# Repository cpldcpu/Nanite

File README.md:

Nanite 85 
======

The Nanite 85, a nano-sized ATtiny85 devboard with USB Bootloader - most likely the smallest one ever.

The repository holds the Eagle circuit, PCB design data and a software example to handle the soft reset-button.

See [Blog post](http://cpldcpu.wordpress.com/2014/04/25/the-nanite-85/) for more information.

New
===

I teamed up with [Watterott](http://www.watterott.com) on making the Nanite 85 available for everyone. You can get one [here](http://www.watterott.com/de/Wattuino-Nanite85). Note that changes had to be made for manufacturability.

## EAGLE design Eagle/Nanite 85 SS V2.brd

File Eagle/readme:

Version 2 of the Single Sided Layout

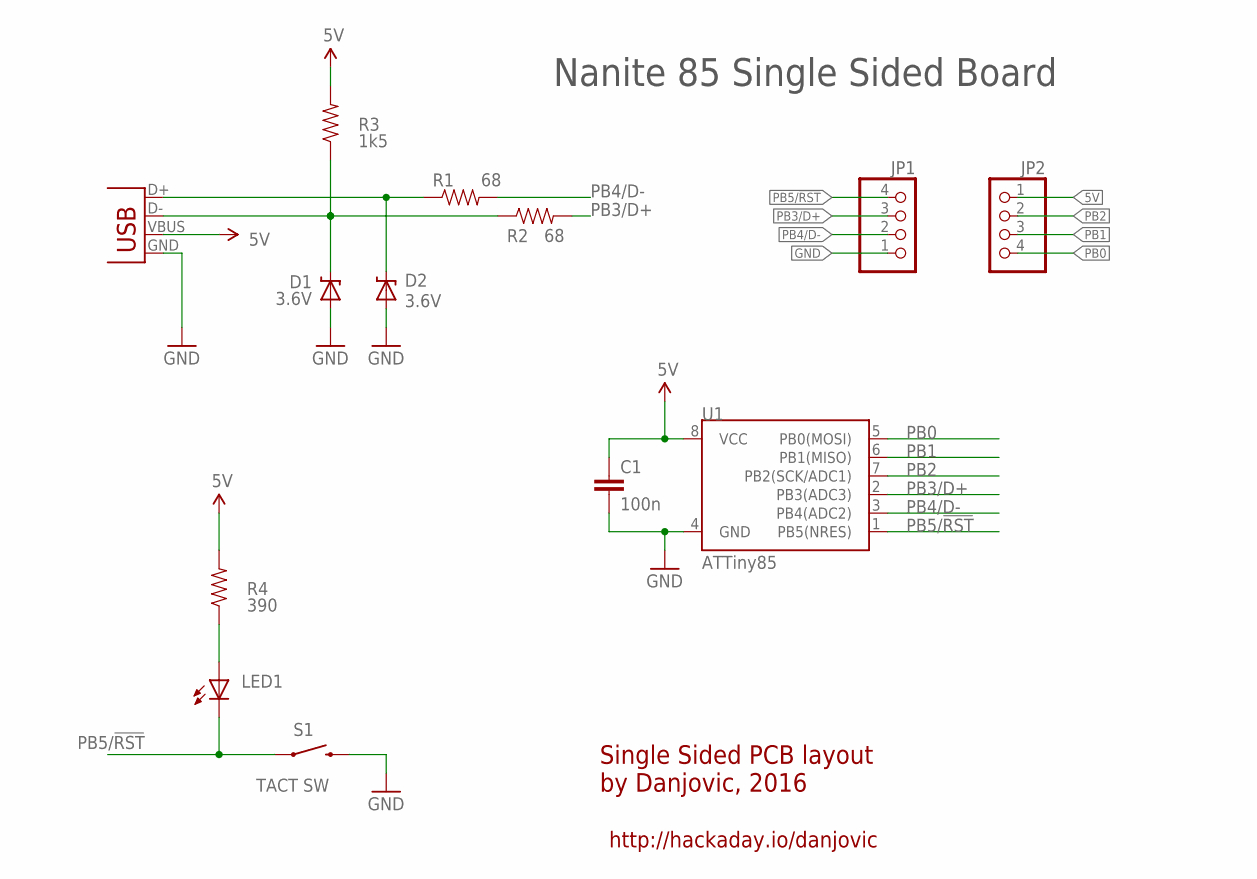
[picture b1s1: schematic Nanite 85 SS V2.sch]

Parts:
C1: 100n; CAP-PTH-SMALL-KIT
D1, D2: 3.6V; DIODE-ZENER
JP1, JP2: HEADER-1X4ROUND; 1X04_ROUND
JP4: USB-B; USB-B-PTH
LED1: LED3MM
R1: 68; AXIAL-0.3
R2: 68; AXIAL-0.3EZ
R3: 1k5; AXIAL-0.3EZ
R4: 390; AXIAL-0.3EZ
S1: TACT SW; TACTILE-PTH
U1: ATTiny85; DIP08

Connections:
5V: C1.1, JP2.1, JP4.VBUS, R3.P$2 (2), R4.P$2 (2), U1.8 (VCC)
GND: C1.2, D1.P$2 (A), D2.P$2 (A), JP1.1, JP4.GND, S1.3 (2), U1.4 (GND)
unnamed: LED1.A, R4.P$1 (1)
PB0: JP2.4, U1.5 (PB0(MOSI))
PB1: JP2.3, U1.6 (PB1(MISO))
PB2: JP2.2, U1.7 (PB2(SCK/ADC1))
PB3/D+: JP1.3, R2.P$2 (2), U1.2 (PB3(ADC3))
PB4/D-: JP1.2, R1.P$2 (2), U1.3 (PB4(ADC2))
PB5/!RST: JP1.4, LED1.K (C), S1.1, U1.1 (PB5(NRES))
USB_D+: D2.P$1 (C), JP4.D+, R1.P$1 (1)
USB_D-: D1.P$1 (C), JP4.D-, R2.P$1 (1), R3.P$1 (1)

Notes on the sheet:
Nanite 85 Single Sided Board
Single Sided PCB layout by Danjovic, 2016
http://hackaday.io/danjovic

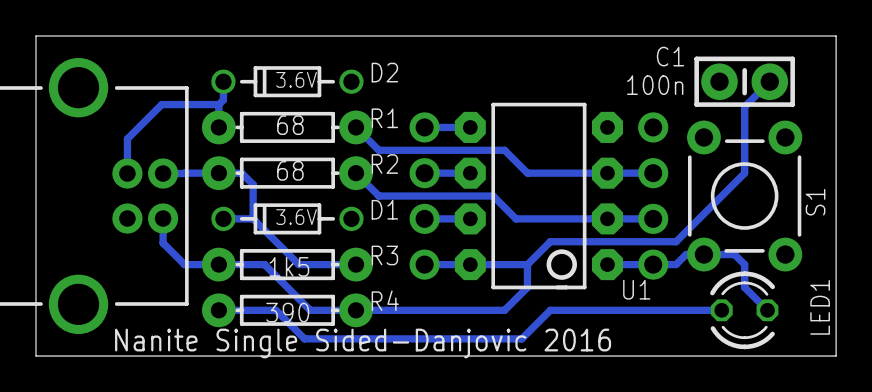
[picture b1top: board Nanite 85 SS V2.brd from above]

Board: 2 copper layers, 44.5 x 17.8 mm, 13 parts (0 on the bottom side), 11 nets.

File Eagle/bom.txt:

Part     Value                         Device                        Package               
C1       100n                          CAP0805                       0805                 
D1       3.6V                          DIODE-ZENER-BZT52             SOD-323               
D2       3.6V                          DIODE-ZENER-BZT52             SOD-323               
JP1                                    HEADER-1X4ROUND               1X04_ROUND            
JP2                                    HEADER-1X4ROUND               1X04_ROUND            
JP4      USB-MICROB-HOLE               USB-MICROB-HOLE               USB-MICROB-HOLES      
LED1                                   LEDCHIPLED_0805               CHIPLED_0805          
R1       68                            RESISTOR0805-RES              0805                  
R2       68                            RESISTOR0805-RES              0805                  
R3       1k5                           RESISTOR0805-RES              0805                  
R4       390                           RESISTOR0805-RES              0805                  
S1       SWITCH-MOMENTARY-2-SMD-1101NE SWITCH-MOMENTARY-2-SMD-1101NE TACTILE-SWITCH-1101NE 
U6       ATTINY85-SSU                  ATTINY45TINY85-20-SMT         SOIC08           

Notes: 
- This is not an easy soldering project! Recommended order is: 1) Rear side 2) Front side 3) Headears
- The USB micro-b socket is a version that come with two alignment pins. It also works without, but is less mechanically stable.
- The tolerances for mounting of the processor are very tight. Make sure it is aligned properly or you will not be able to install the headers.

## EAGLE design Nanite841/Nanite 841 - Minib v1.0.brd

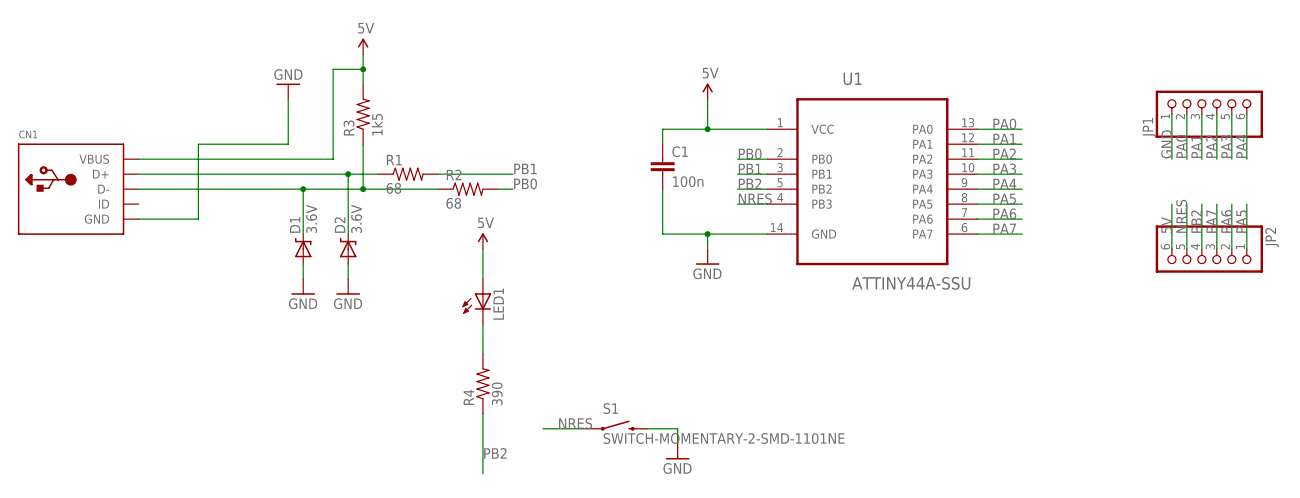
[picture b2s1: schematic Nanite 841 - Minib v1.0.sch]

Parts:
C1: 100n; 0805
CN1: USBMINIB; USB-MINIB
D1, D2: 3.6V; SOD-323
JP1, JP2: HEADER-1X6ROUND; 1X06_ROUND
LED1: LEDCHIPLED_0805; CHIPLED_0805
R1, R2: 68; 0805
R3: 1k5; 0805
R4: 390; 0805
S1: SWITCH-MOMENTARY-2-SMD-1101NE; TACTILE-SWITCH-1101NE
U1: ATTINY44A-SSU; SOIC127P600X175-14N

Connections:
5V: C1.1, CN1.VBUS, JP2.6, LED1.A, R3.2, U1.1 (VCC)
GND: C1.2, CN1.GND, D1.2 (A), D2.2 (A), JP1.1, S1.P$2 (2), U1.14 (GND)
unnamed: CN1.D-, D1.1 (C), R2.1, R3.1
unnamed: CN1.D+, D2.1 (C), R1.1
unnamed: LED1.C, R4.2
NRES: JP2.5, S1.P$1 (1), U1.4 (PB3)
PA0: JP1.2, U1.13 (PA0)
PA1: JP1.3, U1.12 (PA1)
PA2: JP1.4, U1.11 (PA2)
PA3: JP1.5, U1.10 (PA3)
PA4: JP1.6, U1.9 (PA4)
PA5: JP2.1, U1.8 (PA5)
PA6: JP2.2, U1.7 (PA6)
PA7: JP2.3, U1.6 (PA7)
PB0: R2.2, U1.2 (PB0)
PB1: R1.2, U1.3 (PB1)
PB2: JP2.4, R4.1, U1.5 (PB2)

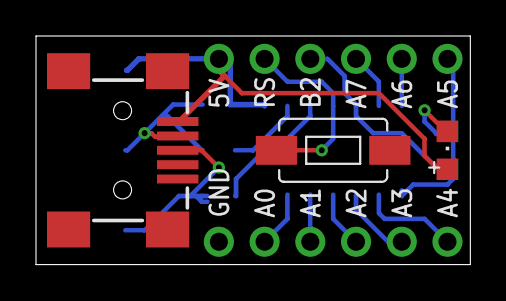
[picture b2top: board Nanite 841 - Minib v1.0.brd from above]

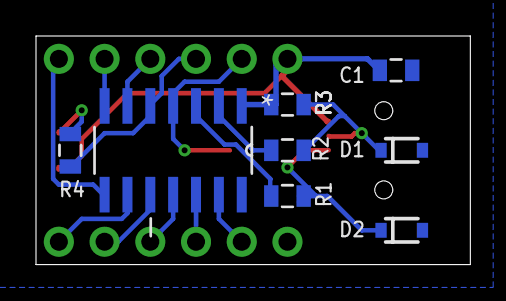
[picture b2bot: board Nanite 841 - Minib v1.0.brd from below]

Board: 2 copper layers, 24.1 x 12.7 mm, 13 parts (8 on the bottom side), 17 nets.

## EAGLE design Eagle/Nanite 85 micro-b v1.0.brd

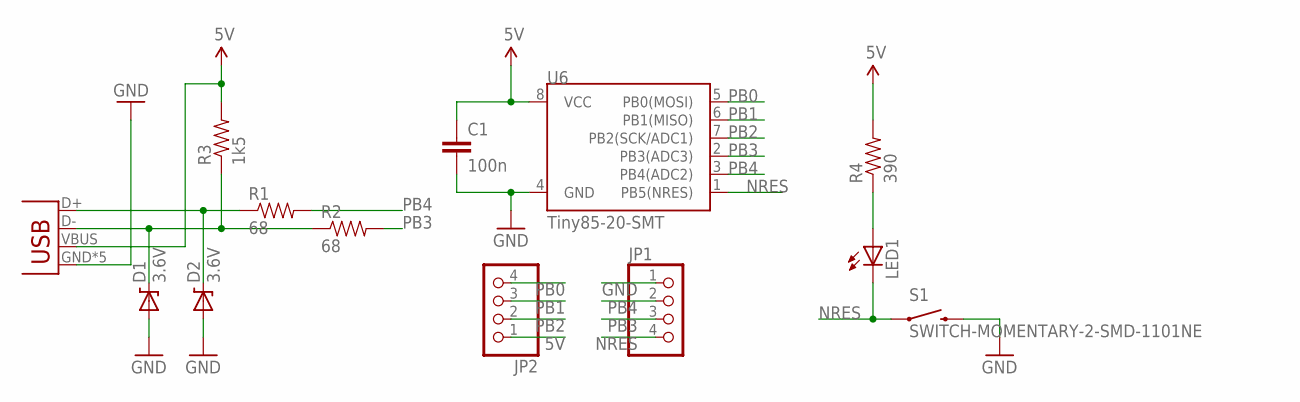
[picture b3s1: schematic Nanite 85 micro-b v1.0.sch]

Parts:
C1: 100n; 0805
D1, D2: 3.6V; SOD-323
JP1, JP2: HEADER-1X4ROUND; 1X04_ROUND
JP4: USB-MICROB-HOLE-ALLCONNECTED; USB-MICROB-HOLES
LED1: LEDCHIPLED_0805; CHIPLED_0805
R1, R2: 68; 0805
R3: 1k5; 0805
R4: 390; 0805
S1: SWITCH-MOMENTARY-2-SMD-1101NE; TACTILE-SWITCH-1101NE
U6: Tiny85-20-SMT; SO08-EIAJ

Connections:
5V: C1.1, JP2.1, JP4.VBUS, R3.2, R4.2, U6.8 (VCC)
GND: C1.2, D1.2 (A), D2.2 (A), JP1.1, JP4.GND, JP4.MT1 (GND), JP4.MT2 (GND), JP4.P$1 (GND), JP4.P$2 (GND), S1.P$2 (2), U6.4 (GND)
unnamed: D1.1 (C), JP4.D-, R2.1, R3.1
unnamed: D2.1 (C), JP4.D+, R1.1
unnamed: LED1.A, R4.1
NRES: JP1.4, LED1.C, S1.P$1 (1), U6.1 (PB5(NRES))
PB0: JP2.4, U6.5 (PB0(MOSI))
PB1: JP2.3, U6.6 (PB1(MISO))
PB2: JP2.2, U6.7 (PB2(SCK/ADC1))
PB3: JP1.3, R2.2, U6.2 (PB3(ADC3))
PB4: JP1.2, R1.2, U6.3 (PB4(ADC2))

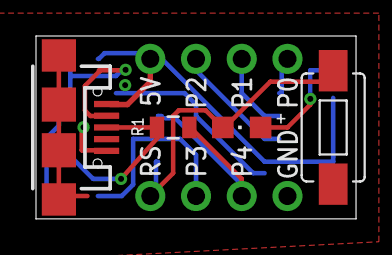
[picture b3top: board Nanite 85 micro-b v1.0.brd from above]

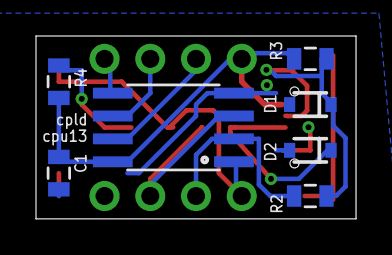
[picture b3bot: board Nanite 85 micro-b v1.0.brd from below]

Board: 2 copper layers, 17.8 x 10.2 mm, 13 parts (7 on the bottom side), 11 nets.

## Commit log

2014-04-25 readme
2014-05-08 added bom
2015-02-08 Nanite 841 first commit
2016-09-24 Single sided PCB layout
    Single sided PCB layout with pass through components.
2016-09-26 Version 2 of the Single Sided layout
    Rotated the AVR in 90 degrees and moved the push button to the edge of the board
2016-09-26 Creation of the directory
2016-09-26 wrong folder

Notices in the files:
parts and their libraries:
SparkFun-DigitalIC: Licensing: CC v3.0 Share-Alike You are welcome to use this library for commercial purposes.
microbuilder: This work is placed in the public domain, and may be freely used for commercial and non-commercial work with the following conditions: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
